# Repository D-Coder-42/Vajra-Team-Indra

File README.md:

# Project Vajra
## By Team Indra

### Table of Contents
- [Team Members](#team-members)
- [Abstract](#abstract)
- [Introduction](#introduction)
- [Goals](#goals)

### Team Members
- **Shaurya Mittal** - Aerodynamics Member
- **Shaunak Purkayastha** - Propulsion Member
- **Tushit Chatterjee** - Structures Member
- **Krishanu Dey** - Avionics Member
- **Dhruv Phalod** - Avionics Member
- **Vanshdeep Trivedi** - Avionics Member
- **Mutra Sai Tharun** - Payload Member
- **Rudra Rajpurohit** - Payload Member
- **Swaraa Sule** - Management Member
- **Adithya Adiga** - Management Member

### Project Abstract
Team Indra’s rocket, Vajra, is powered by an N3452 N-class SRAD rocket motor. Its internal frame is made from Aluminum 6061, and the aerodynamic structure combines Carbon Fibre and Glass Fibre for optimal performance. The nosecone houses a CanSat payload with a GIMBAL-controlled platform, attached via springs to withstand rocket vibrations. An onboard microcontroller ensures the platform is positioned to keep a PYRAMID object aligned with the camera’s center for tracking the entire flight. The avionics use Surface Mount Technology (SMT) components, with two microcontrollers handling tasks like data logging, apogee detection, recovery control, and airbrake activation. The flight computer supports real-time telemetry up to 16 kilometers, transmitting flight dynamics and GPS data.

### Team Introduction
Team Indra is a student-run rocketry team based in Manipal, India. We are named after one of the mightiest and strongest gods in Hindu mythology. With access to state-of-the-art resources and immense hard work, our diverse and talented team is exceptionally equipped to tackle the complex engineering challenges of rocketry. Our mission is to create a fully functional sounding rocket that reaches a height of 10,000 feet. We are dedicated to using our collective creativity and determination to fulfill our purpose and further develop groundbreaking solutions that advance the field of aerospace engineering.

### Goals
- Develop a fully functional sounding rocket.
- Achieve a flight altitude of 10,000 feet.
- Innovate in the fields of aerodynamics, propulsion, and avionics.

###
All codes and files for Team B of thrustMIT subscale are included in this repository.

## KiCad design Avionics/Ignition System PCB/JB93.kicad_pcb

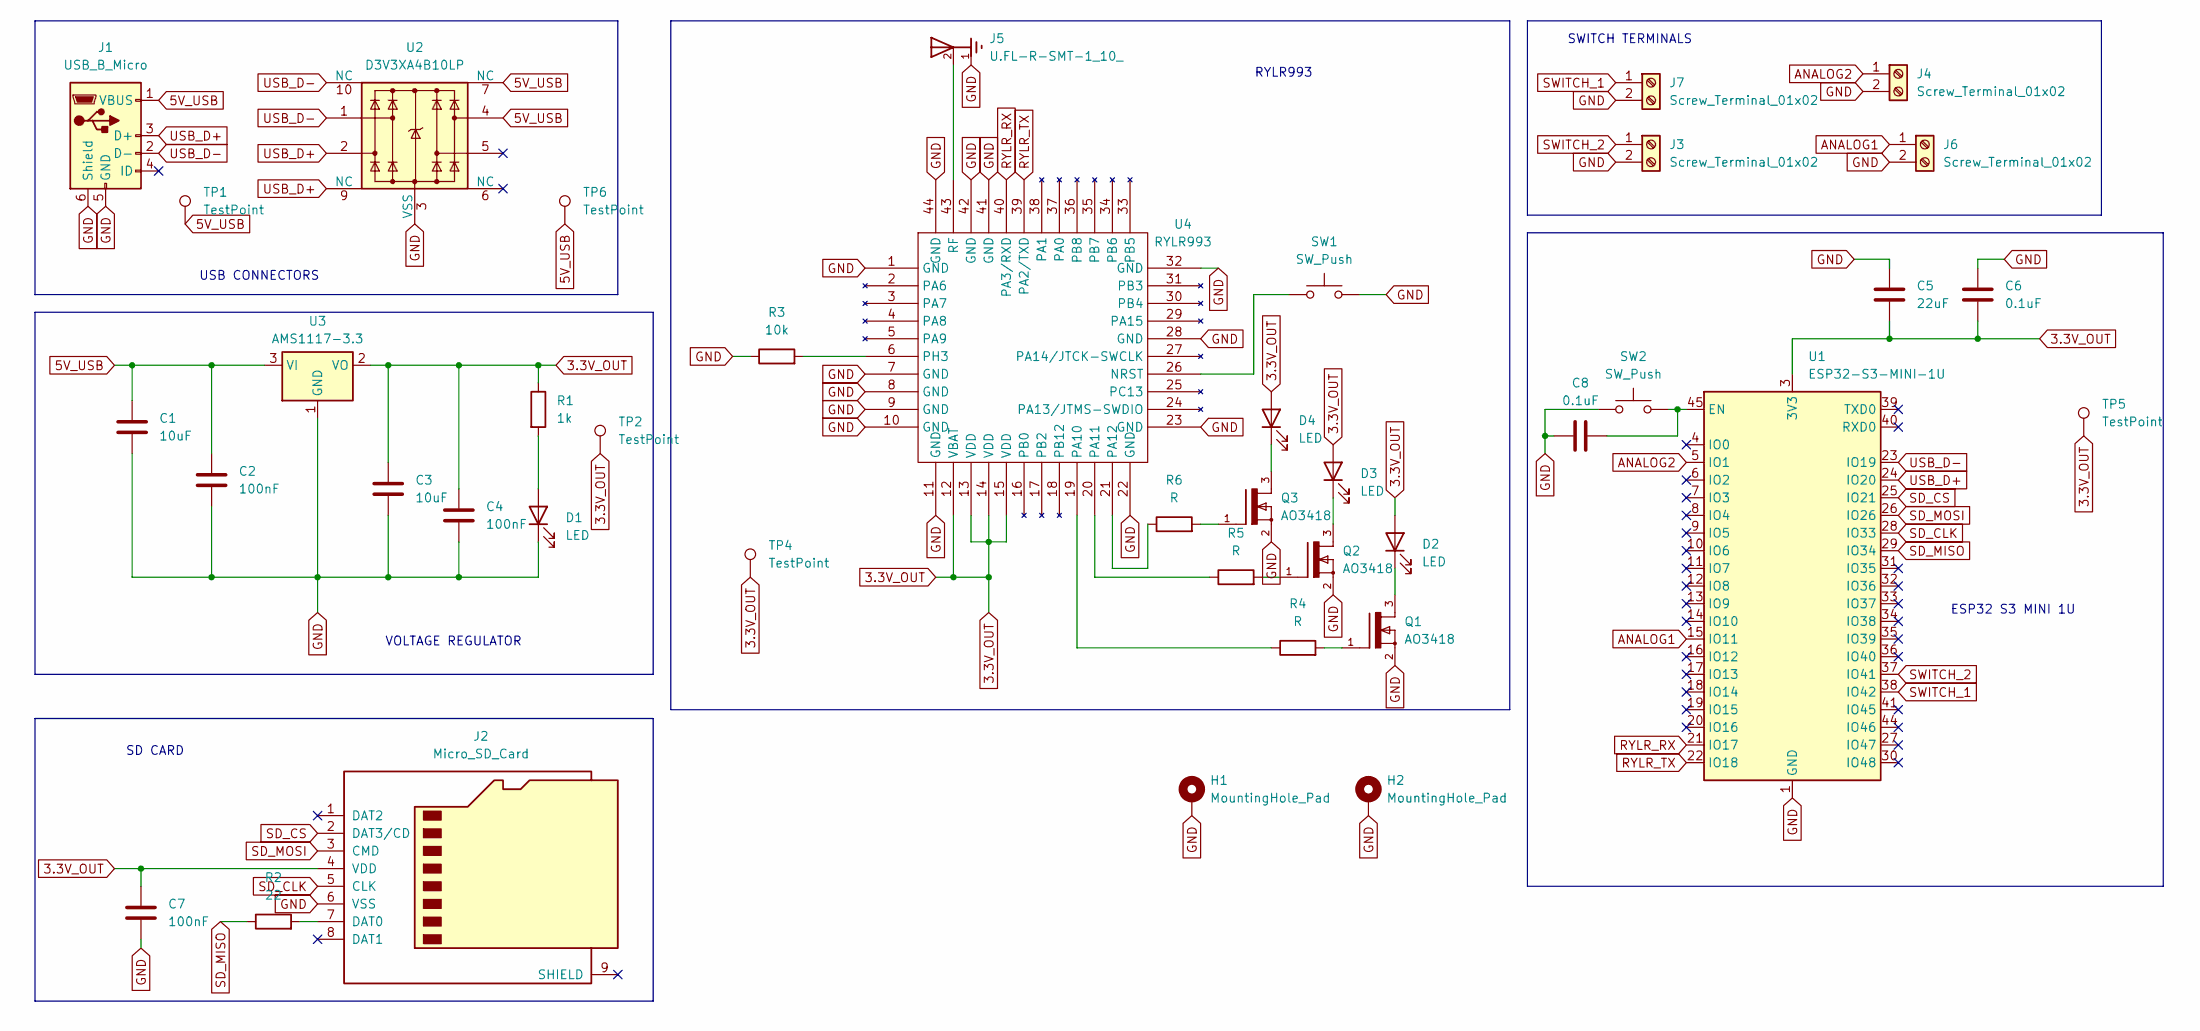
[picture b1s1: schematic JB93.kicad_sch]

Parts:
C1, C3: 10uF; C_0201_0603Metric
C2, C4, C7: 100nF; C_0201_0603Metric
C5: 22uF; C_0201_0603Metric
C6, C8: 0.1uF; C_0201_0603Metric
D1, D2, D3, D4: LED; LED_miniPLCC_2315
H1, H2: MountingHole_Pad; MountingHole_4.3mm_M4_DIN965_Pad
J1: USB_B_Micro; USB_Micro-B_GCT_USB3076-30-A
J2: Micro_SD_Card; microSD_HC_Hirose_DM3BT-DSF-PEJS
J3, J4, J6, J7: Screw_Terminal_01x02; TerminalBlock_Xinya_XY308-2.54-2P_1x02_P2.54mm_Horizontal
J5: U.FL-R-SMT-1_10_; U.FL_Hirose_U.FL-R-SMT-1_Vertical
Q1, Q2, Q3: AO3418; SOT-23
R1: 1k; R_0201_0603Metric
R2: 22; R_0201_0603Metric
R3: 10k; R_0201_0603Metric
R4, R5, R6: R; R_0201_0603Metric
SW1, SW2: SW_Push; SW_Tactile_SPST_NO_Straight_CK_PTS636Sx25SMTRLFS
TP1, TP2, TP4, TP5, TP6: TestPoint; TestPoint_Pad_1.0x1.0mm
U1: ESP32-S3-MINI-1U; ESP32-S2-MINI-1U
U2: D3V3XA4B10LP; Diodes_UDFN-10_1.0x2.5mm_P0.5mm
U3: AMS1117-3.3; SOT-223-3_TabPin2
U4: RYLR993

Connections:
3.3V_OUT: C3.1, C4.1, C5.2, C6.2, C7.1, D2.2 (A), D3.2 (A), D4.2 (A), J2.4 (VDD), R1.1, TP2.1, TP4.1, TP5.1, U1.3 (3V3), U3.2 (VO), U4.12 (VBAT), U4.13 (VDD), U4.14 (VDD), U4.15 (VDD)
5V_USB: C1.1, C2.1, J1.1 (VBUS), TP1.1, TP6.1, U2.4, U2.7 (NC), U3.3 (VI)
ANALOG1: J6.1, U1.15 (IO11)
ANALOG2: J4.1, U1.5 (IO1)
GND: C1.2, C2.2, C3.2, C4.2, C5.1, C6.1, C7.2, C8.1, D1.1 (K), H1.1, H2.1, J1.5 (GND), J1.6 (Shield), J2.6 (VSS), J3.2, J4.2, J5.1, J6.2, J7.2, Q1.2, Q2.2, Q3.2, R3.1, SW1.2, SW2.1, U1.1 (GND), U1.2 (GND), U1.42 (GND), U1.43 (GND), U1.46 (GND), U1.47 (GND), U1.48 (GND), U1.49 (GND), U1.50 (GND), U1.51 (GND), U1.52 (GND), U1.53 (GND), U1.54 (GND), U1.55 (GND), U1.56 (GND), U1.57 (GND), U1.58 (GND), U1.59 (GND), U1.60 (GND), U1.61 (GND), U1.62 (GND), U1.63 (GND), U1.64 (GND), U1.65 (GND), U2.3 (VSS), U2.8 (VSS), U3.1 (GND), U4.1 (GND), U4.7 (GND), U4.8 (GND), U4.9 (GND), U4.10 (GND), U4.11 (GND), U4.22 (GND), U4.23 (GND), U4.28 (GND), U4.32 (GND), U4.41 (GND), U4.42 (GND), U4.44 (GND)
unnamed: D1.2 (A), R1.2
unnamed: D2.1 (K), Q1.3
unnamed: D3.1 (K), Q2.3
unnamed: D4.1 (K), Q3.3
unnamed: J2.7 (DAT0), R2.2
unnamed: Q1.1, R4.2
unnamed: Q2.1, R5.2
unnamed: Q3.1, R6.2
unnamed: C8.2, SW2.2, U1.45 (EN)
unnamed: SW1.1, U4.26 (NRST)
unnamed: R4.1, U4.19 (PA10)
unnamed: R5.1, U4.20 (PA11)
unnamed: R6.1, U4.21 (PA12)
unnamed: R3.2, U4.6 (PH3)
unnamed: J5.2, U4.43 (RF)
RYLR_RX: U1.21 (IO17), U4.40 (PA3/RXD)
RYLR_TX: U1.22 (IO18), U4.39 (PA2/TXD)
SD_CLK: J2.5 (CLK), U1.28 (IO33)
SD_CS: J2.2 (DAT3/CD), U1.25 (IO21)
SD_MISO: R2.1, U1.29 (IO34)
SD_MOSI: J2.3 (CMD), U1.26 (IO26)
SWITCH_1: J7.1, U1.38 (IO42)
SWITCH_2: J3.1, U1.37 (IO41)
USB_D+: J1.3 (D+), U1.24 (IO20), U2.2, U2.9 (NC)
USB_D-: J1.2 (D-), U1.23 (IO19), U2.1, U2.10 (NC)

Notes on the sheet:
VOLTAGE REGULATOR
SD CARD
RYLR993
USB CONNECTORS
SWITCH TERMINALS
ESP32 S3 MINI 1U

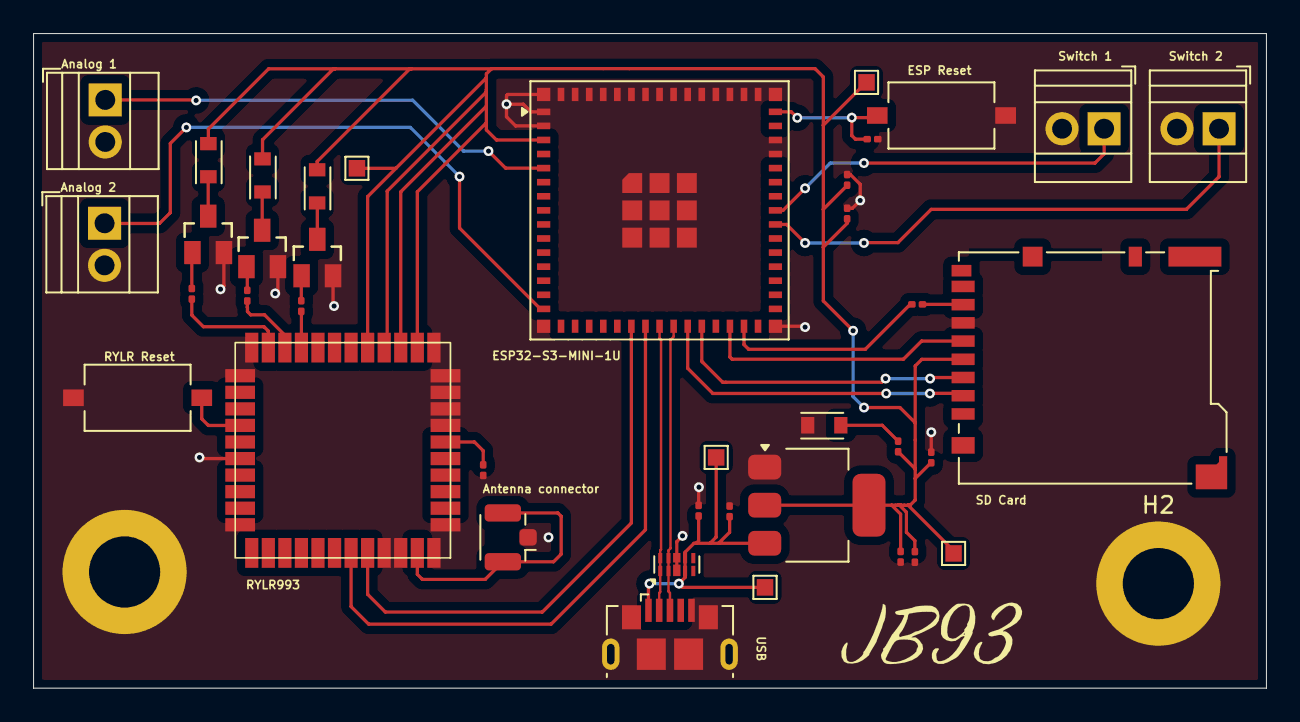
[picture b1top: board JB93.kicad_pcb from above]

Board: 2 copper layers, 74.5 x 39.5 mm, 41 parts (0 on the bottom side), 30 nets.

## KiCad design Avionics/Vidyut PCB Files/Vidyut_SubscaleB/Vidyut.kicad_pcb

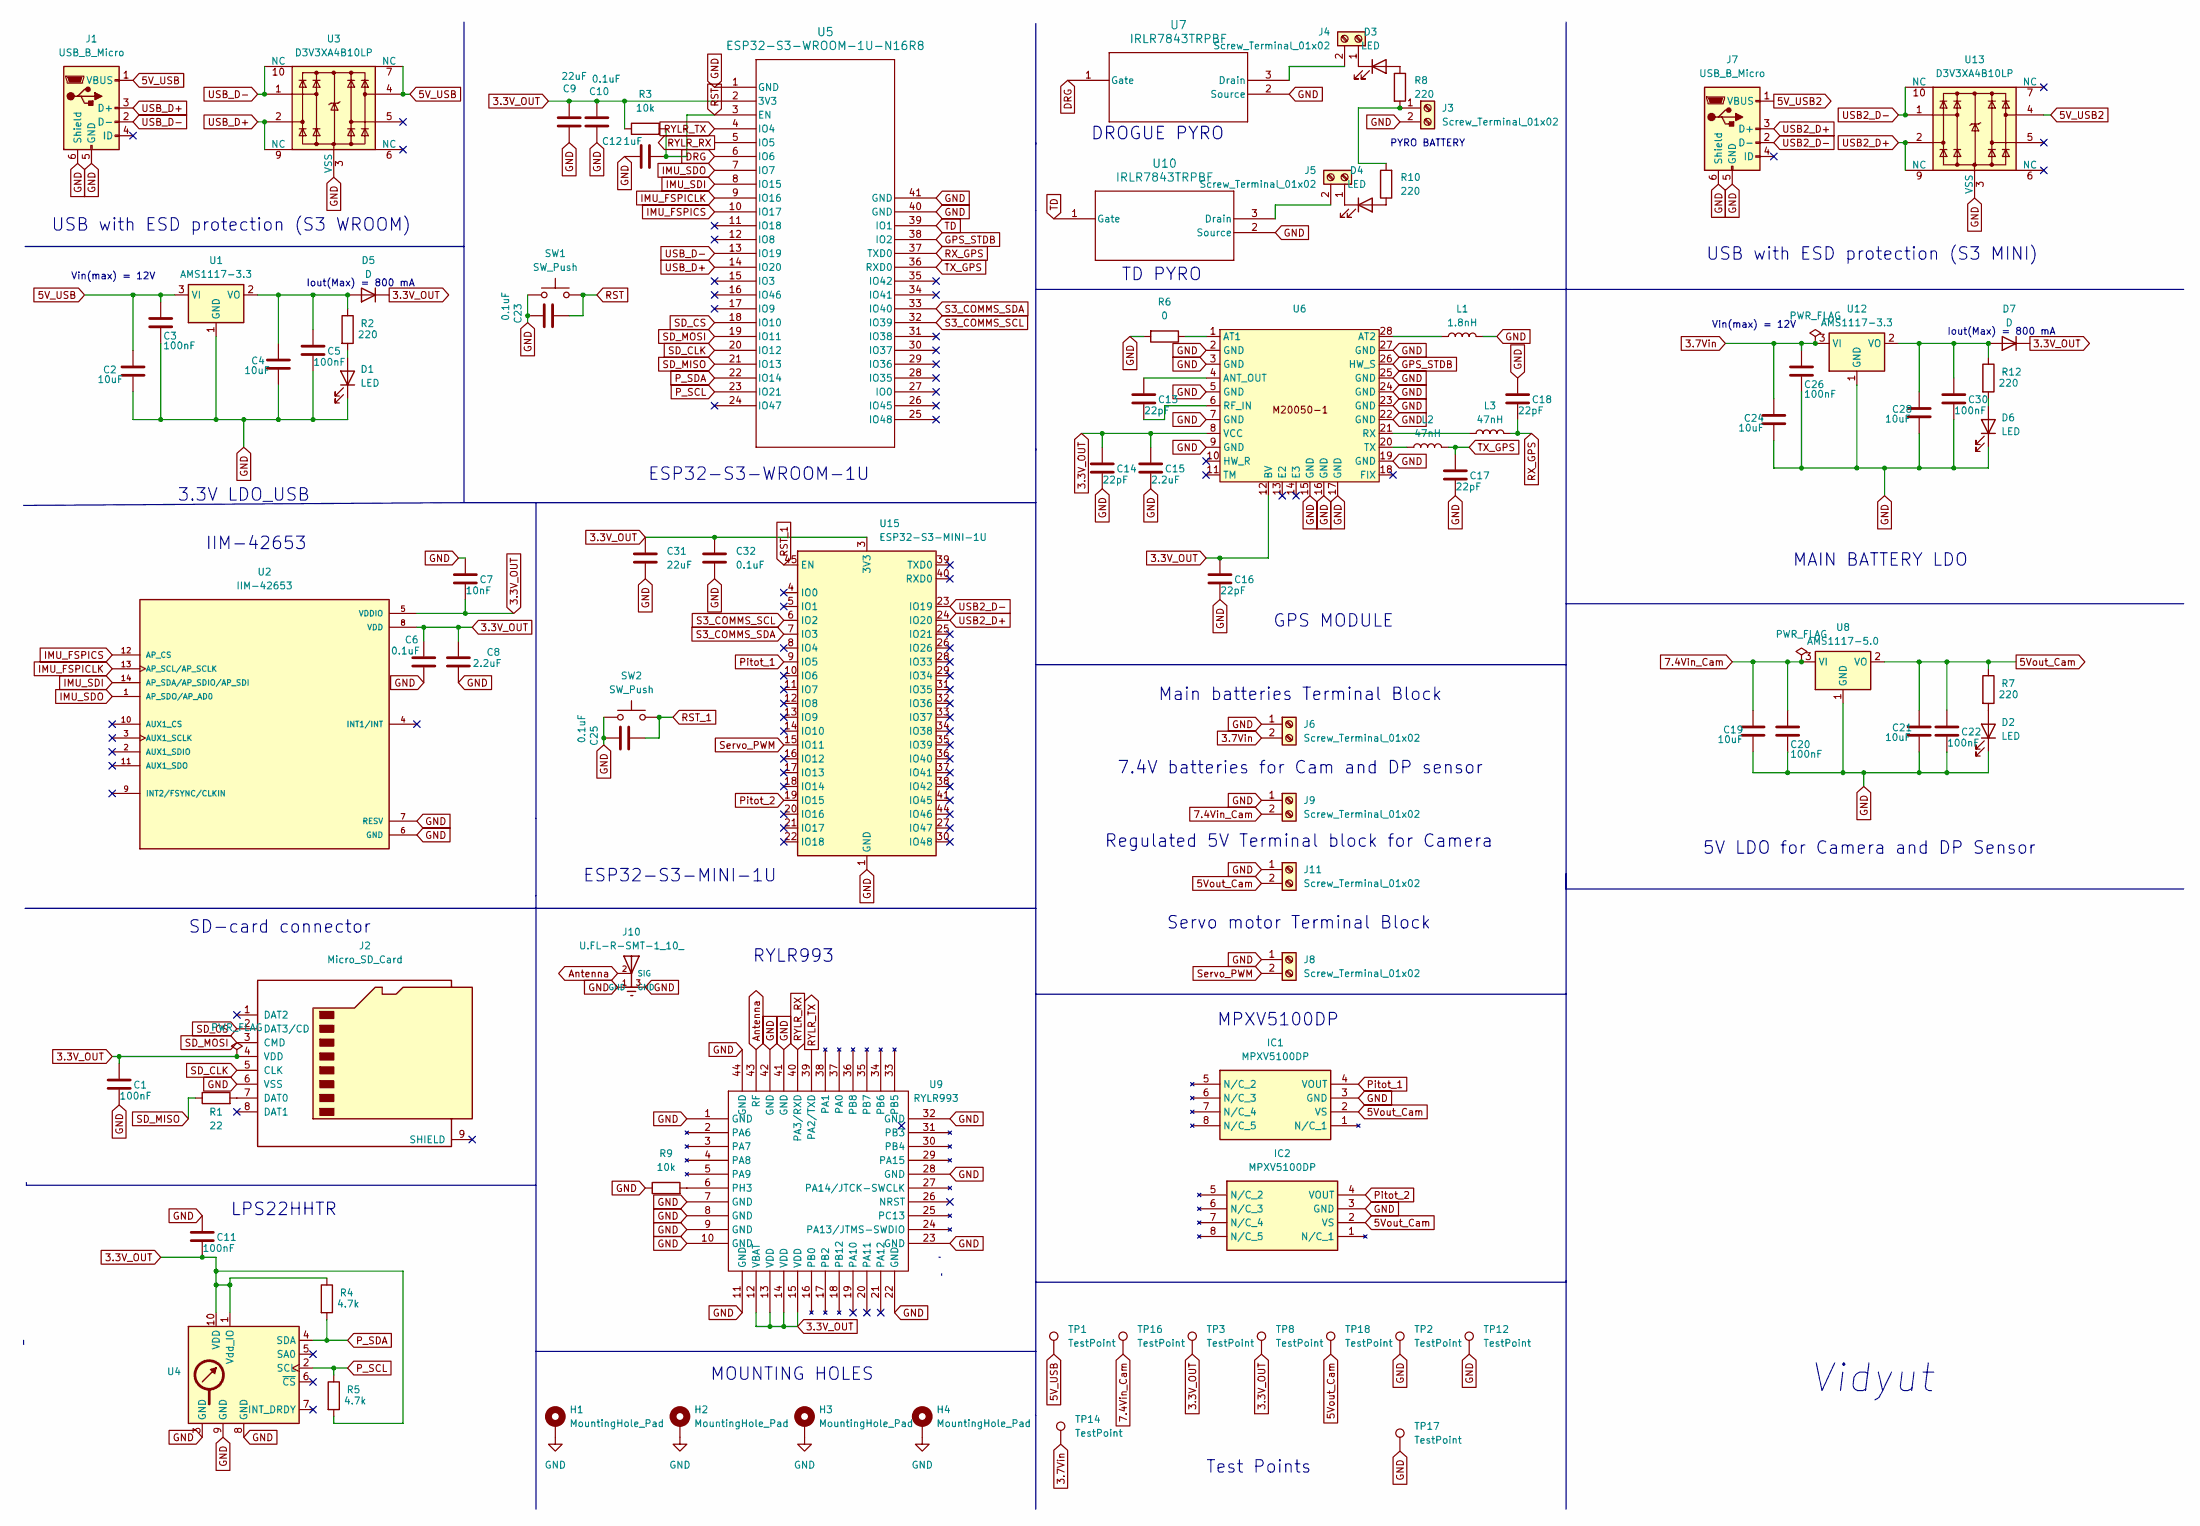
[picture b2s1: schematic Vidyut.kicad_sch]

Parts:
C1, C3, C5, C11, C20, C22, C26, C30: 100nF; C_0805_2012Metric
C2, C4, C19, C21, C24, C28: 10uF; C_0805_2012Metric
C6, C10, C23, C25, C32: 0.1uF; C_0805_2012Metric
C7: 10nF; C_0805_2012Metric
C8, C15: 2.2uF; C_0805_2012Metric
C9, C31: 22uF; C_0805_2012Metric
C12: 1uF; C_0805_2012Metric
C13, C14, C16, C17, C18: 22pF; C_0805_2012Metric
D1, D2, D3, D4, D6: LED; LED_0805_2012Metric
D5, D7: D; D_0805_2012Metric
H1, H2, H3, H4: MountingHole_Pad; MountingHole_4.3mm_M4_DIN965_Pad
IC1, IC2: MPXV5100DP; Manufacturer_Part_Number MPXV5100DP; Mouser Part Number 841-MPXV5100DP
J1, J7: USB_B_Micro; USB_Micro-B_GCT_USB3076-30-A
J2: Micro_SD_Card; microSD_HC_Hirose_DM3BT-DSF-PEJS
J3, J4, J5, J6, J8, J9, J11: Screw_Terminal_01x02; TerminalBlock_bornier-2_P5.08mm
J10: U.FL-R-SMT-1_10_; RYLR993 Antenna connector
L1: 1.8nH; L_0805_2012Metric
L2, L3: 47nH; L_0805_2012Metric
R1: 22; R_0805_2012Metric
R2, R7, R8, R10, R12: 220; R_0805_2012Metric
R3, R9: 10k; R_0805_2012Metric
R4, R5: 4.7k; R_0805_2012Metric
R6: 0; R_0805_2012Metric
SW1, SW2: SW_Push; SW_Tactile_SPST_NO_Straight_CK_PTS636Sx25SMTRLFS
TP1, TP2, TP3, TP8, TP12, TP14, TP16, TP17, TP18: TestPoint; TestPoint_Pad_D1.0mm
U1, U12: AMS1117-3.3; SOT-223-3_TabPin2
U2: IIM-42653; IIM-42652_TDK; PARTREV 1.1
U3, U13: D3V3XA4B10LP; Diodes_UDFN-10_1.0x2.5mm_P0.5mm
U4: LPS22HHTR_3
U5: ESP32-S3-WROOM-1U-N16R8; ESP32-S3-WROOM-1U
U6: M20050 GPS
U7, U10: IRLR7843TRPBF
U8: AMS1117-5.0; SOT-223-3_TabPin2
U9: RYLR993
U15: ESP32-S3-MINI-1U; ESP32-S2-MINI-1U

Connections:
3.3V_OUT: C1.1, C6.1, C7.2, C8.1, C9.1, C10.1, C11.2, C14.1, C15.1, C16.1, C31.1, C32.1, D5.1 (K), D7.1 (K), J2.4 (VDD), R3.1, R4.1, R5.2, TP3.1, TP8.1, U2.5 (VDDIO), U2.8 (VDD), U4.1 (Vdd_IO), U4.10 (VDD), U5.2 (3V3), U6.8 (VCC), U6.12 (BV), U9.12 (VBAT), U9.13 (VDD), U9.14 (VDD), U9.15 (VDD), U15.3 (3V3)
3.7Vin: C24.1, C26.1, J6.2, TP14.1, U12.3 (VI)
5V_USB: C2.1, C3.1, J1.1 (VBUS), TP1.1, U1.3 (VI), U3.4, U3.7 (NC)
5V_USB2: J7.1 (VBUS), U13.4
5Vout_Cam: C21.1, C22.1, IC1.2 (VS), IC2.2 (VS), J11.2, R7.1, TP18.1, U8.2 (VO)
7.4Vin_Cam: C19.1, C20.1, J9.2, TP16.1, U8.3 (VI)
Antenna: J10.2 (SIG), U9.43 (RF)
DRG: U5.6 (IO6), U7.1 (Gate)
GND: C1.2, C2.2, C3.2, C4.2, C5.2, C6.2, C7.1, C8.2, C9.2, C10.2, C11.1, C12.1, C14.2, C15.2, C16.2, C17.2, C18.1, C19.2, C20.2, C21.2, C22.2, C23.1, C24.2, C25.1, C26.2, C28.2, C30.2, C31.2, C32.2, D1.1 (K), D2.1 (K), D6.1 (K), H1.1, H2.1, H3.1, H4.1, IC1.3 (GND), IC2.3 (GND), J1.5 (GND), J1.6 (Shield), J2.6 (VSS), J3.2, J6.1, J7.5 (GND), J7.6 (Shield), J8.1, J9.1, J10.1 (GND), J10.3 (GND), J11.1, L1.2, R6.2, R9.1, SW1.1, SW2.1, TP2.1, TP12.1, TP17.1, U1.1 (GND), U2.6 (GND), U2.7 (RESV), U3.3 (VSS), U3.8 (VSS), U4.3 (GND), U4.8 (GND), U4.9 (GND), U5.1 (GND), U5.40 (GND), U5.41 (GND), U6.2 (GND), U6.3 (GND), U6.5 (GND), U6.7 (GND), U6.9 (GND), U6.15 (GND), U6.16 (GND), U6.17 (GND), U6.19 (GND), U6.22 (GND), U6.23 (GND), U6.24 (GND), U6.25 (GND), U6.27 (GND), U7.2 (Source), U8.1 (GND), U9.1 (GND), U9.7 (GND), U9.8 (GND), U9.9 (GND), U9.10 (GND), U9.11 (GND), U9.22 (GND), U9.23 (GND), U9.28 (GND), U9.32 (GND), U9.41 (GND), U9.42 (GND), U9.44 (GND), U10.2 (Source), U12.1 (GND), U13.3 (VSS), U13.8 (VSS), U15.1 (GND), U15.2 (GND), U15.42 (GND), U15.43 (GND), U15.46 (GND), U15.47 (GND), U15.48 (GND), U15.49 (GND), U15.50 (GND), U15.51 (GND), U15.52 (GND), U15.53 (GND), U15.54 (GND), U15.55 (GND), U15.56 (GND), U15.57 (GND), U15.58 (GND), U15.59 (GND), U15.60 (GND), U15.61 (GND), U15.62 (GND), U15.63 (GND), U15.64 (GND), U15.65 (GND)
GPS_STDB: U5.38 (IO2), U6.26 (HW_S)
IMU_FSPICLK: U2.13 (AP_SCL/AP_SCLK), U5.9 (IO16)
IMU_FSPICS: U2.12 (AP_CS), U5.10 (IO17)
IMU_SDI: U2.14 (AP_SDA/AP_SDIO/AP_SDI), U5.8 (IO15)
IMU_SDO: U2.1 (AP_SDO/AP_AD0), U5.7 (IO7)
unnamed: D1.2 (A), R2.2
unnamed: D2.2 (A), R7.2
unnamed: D3.2 (A), R8.1
unnamed: D3.1 (K), J4.1
unnamed: D4.2 (A), R10.1
unnamed: D4.1 (K), J5.1
unnamed: C4.1, C5.1, D5.2 (A), R2.1, U1.2 (VO)
unnamed: D6.2 (A), R12.2
unnamed: C28.1, C30.1, D7.2 (A), R12.1, U12.2 (VO)
unnamed: J2.7 (DAT0), R1.2
unnamed: J3.1, R8.2, R10.2
unnamed: J4.2, U7.3 (Drain)
unnamed: J5.2, U10.3 (Drain)
unnamed: C13.1, U6.4 (ANT_OUT)
unnamed: R6.1, U6.1 (AT1)
unnamed: L1.1, U6.28 (AT2)
unnamed: C13.2, U6.6 (RF_IN)
unnamed: L3.1, U6.21 (RX)
unnamed: L2.1, U6.20 (TX)
unnamed: R9.2, U9.6 (PH3)
P_SCL: R5.1, U4.2 (SCL), U5.23 (IO21)
P_SDA: R4.2, U4.4 (SDA), U5.22 (IO14)
Pitot_1: IC1.4 (VOUT), U15.9 (IO5)
Pitot_2: IC2.4 (VOUT), U15.19 (IO15)
RST: C12.2, C23.2, R3.2, SW1.2, U5.3 (EN)
RST_1: C25.2, SW2.2, U15.45 (EN)
RX_GPS: C18.2, L3.2, U5.37 (TXD0)
RYLR_RX: U5.5 (IO5), U9.40 (PA3/RXD)
RYLR_TX: U5.4 (IO4), U9.39 (PA2/TXD)
S3_COMMS_SCL: U5.32 (IO39), U15.6 (IO2)
S3_COMMS_SDA: U5.33 (IO40), U15.7 (IO3)
SD_CLK: J2.5 (CLK), U5.20 (IO12)
SD_CS: J2.2 (DAT3/CD), U5.18 (IO10)
SD_MISO: R1.1, U5.21 (IO13)
SD_MOSI: J2.3 (CMD), U5.19 (IO11)
Servo_PWM: J8.2, U15.15 (IO11)
TD: U5.39 (IO1), U10.1 (Gate)
TX_GPS: C17.1, L2.2, U5.36 (RXD0)
USB2_D+: J7.3 (D+), U13.2, U13.9 (NC), U15.24 (IO20)
USB2_D-: J7.2 (D-), U13.1, U13.10 (NC), U15.23 (IO19)
USB_D+: J1.3 (D+), U3.2, U3.9 (NC), U5.14 (IO20)
USB_D-: J1.2 (D-), U3.1, U3.10 (NC), U5.13 (IO19)

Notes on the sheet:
MAIN BATTERY LDO
MPXV5100DP
USB with ESD protection (S3 WROOM)
Iout(Max) = 800 mA
5V LDO for Camera and DP Sensor
Regulated 5V Terminal block for Camera
IIM-42653
PYRO BATTERY
Vidyut
DROGUE PYRO
Servo motor Terminal Block
Main batteries Terminal Block
ESP32-S3-WROOM-1U
MOUNTING HOLES
Test Points
RYLR993
TD PYRO
7.4V batteries for Cam and DP sensor
ESP32-S3-MINI-1U
Vin(max) = 12V
3.3V LDO_USB
USB with ESD protection (S3 MINI)
LPS22HHTR
GPS MODULE
SD-card connector

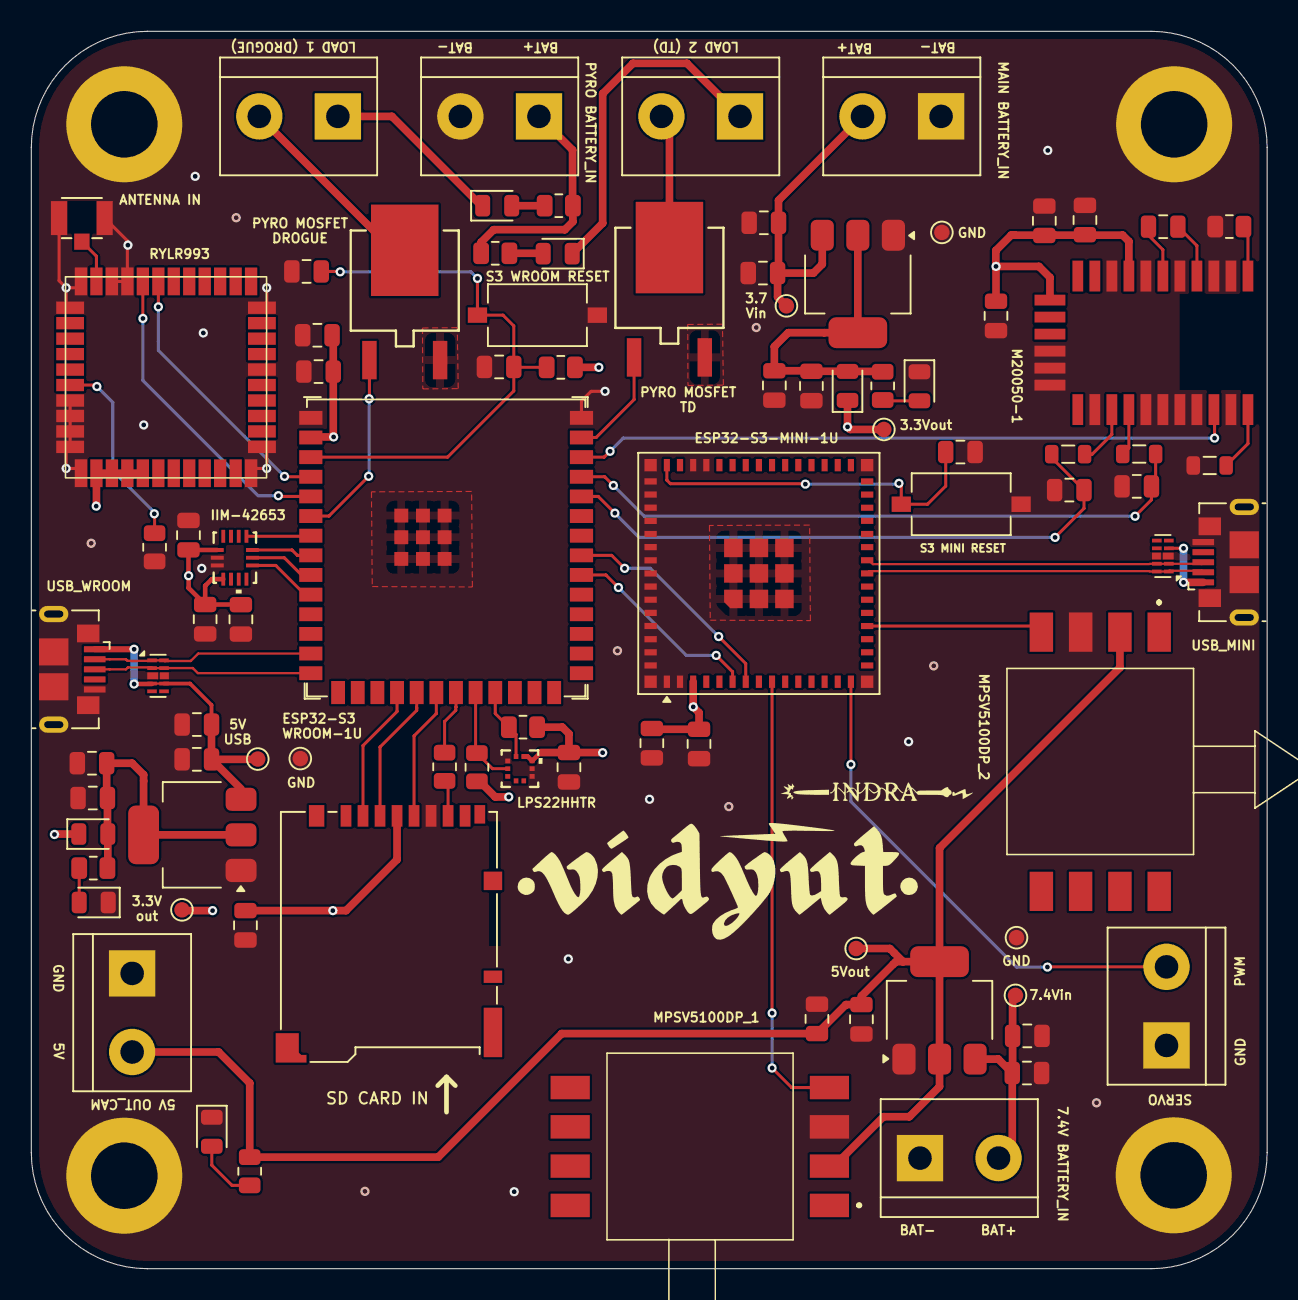
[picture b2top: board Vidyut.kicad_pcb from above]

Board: 4 copper layers, 79.9 x 80.0 mm, 92 parts (0 on the bottom side), 56 nets.

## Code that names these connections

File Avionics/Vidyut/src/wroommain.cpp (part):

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#include <Wire.h>

// Pin Definitions
#define RYLR_RX     1
#define RYLR_TX     2
#define SD_SCK      3
#define SD_MOSI     4
#define SD_MISO     5
#define SD_SS       6
#define IIM_SCK     7
#define IIM_MOSI    8
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
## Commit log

2025-01-15 Added Basic Structure
2025-01-15 Initial ORK design
2025-01-27 Added reference documents
2025-02-16 Added Vidyut code files
2025-02-17 Restructured Documents
2025-02-18 Renamed Folder
2025-02-19 Create Vidyut PCB
2025-02-19 Added FInal Report Supporting Files
2025-03-07 Added .gitignore file
2025-03-07 Relocated PCB files
